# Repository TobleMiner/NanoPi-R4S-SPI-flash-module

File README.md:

NanoPi R4S NOR flash adapter
============================

This PCB provides the NanoPi R4S with NOR flash as a secondary or primary
boot option.  
Compared to most micro SD cards NOR flash is inherently much more reliable
due to its internal structure. While this comes with its own set of
drawbacks notably small storage size and low write speed it is very well
suited for many appliance applications.  
The dual LAN port configuration of the NanoPi R4S makes it a perfect match
for router operations. This NOR flash adapter module could for example be
paired with OpenWRT to provide a highly reliable router platform.

In addition to the SPI flash this board also features an STM32G031G6U6
microcontroller. It is connected to an I2C bus on the NanoPi R4S.  
The MCU has control over the reset and write protect lines of the SPI NOR
flash chip. Thus it can be used to disable the flash chip if booting from
alternate sources is desired. The write-protect line can be used to
implement custom tamper-proof storage designs.

To notify users of operations performed by the MCU a small dynamic
speaker is provided.

# Ordering

**WARNING: Do not order rev1.0 at JLC. The partnumber for the MCU is incorrect!**

The fabrication files inside `fab` are JLCPCB-ready. I'd suggest ordering
with a 1mm board thickness. This will ensure the easiest fit in small
cases.

The board can be fully assmebled by JLC. The required fabrication files
can also be found in the `fab` directory.  
If you do not plan on using the MCU on the board you can simply unselect
the following components on JLC's website during ordering:

- U5
- D1
- LS1
- C4
- C5
- C6

This will make the boards significantly cheaper, especially when ordering
small quantities.

# Installation

Due to space constraints imposed by many cases the recommended
installation method for this board is to solder it directly to the
expansion header of the NanoPi R4S. Make sure to push the board down onto
the expansion header as far as possible before soldering it into place.

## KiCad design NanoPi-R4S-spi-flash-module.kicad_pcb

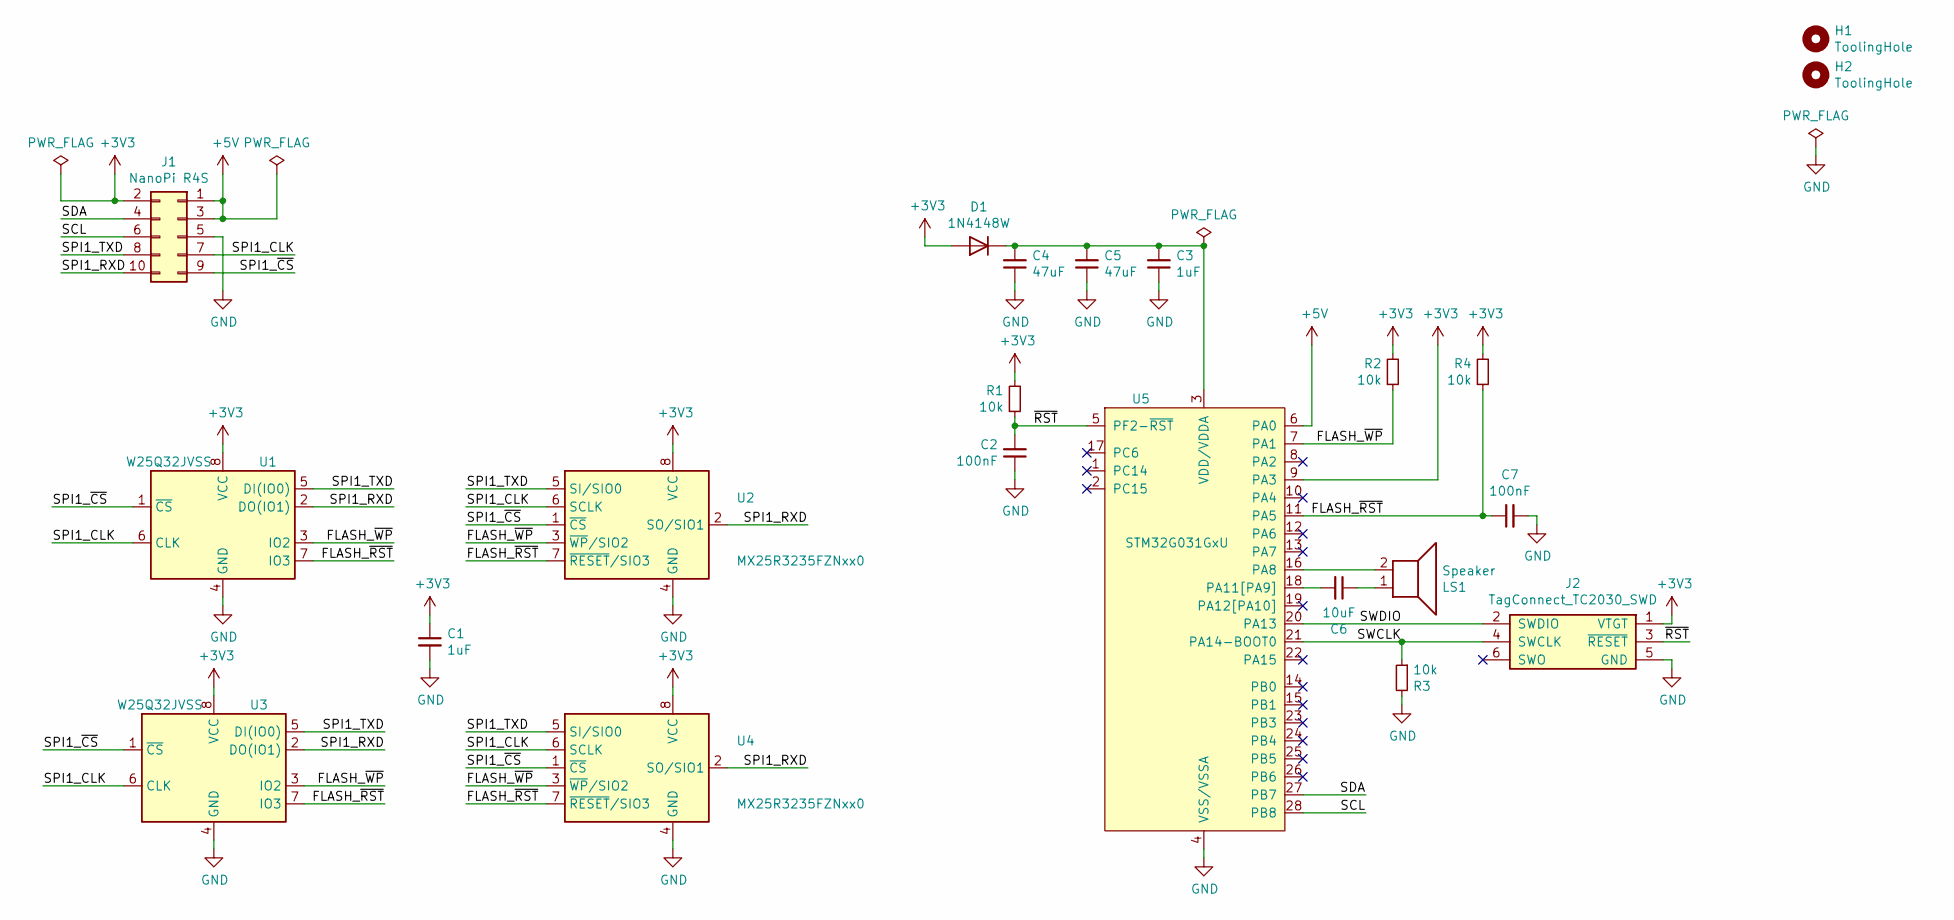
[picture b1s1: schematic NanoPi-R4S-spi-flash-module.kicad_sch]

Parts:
C1, C3: 1uF; C_0402_1005Metric; LCSC C52923
C2, C7: 100nF; C_0402_1005Metric; LCSC C1525
C4, C5: 47uF; C_0603_1608Metric; LCSC C140782
C6: 10uF; C_0402_1005Metric; LCSC C15525
D1: 1N4148W; D_SOD-123; LCSC C81598
H1, H2: ToolingHole; ToolingHole_JLCSMT
J1: NanoPi R4S; PinHeader_2x05_P2.54mm_Vertical
J2: TagConnect_TC2030_SWD; Tag-Connect_TC2030-IDC-NL_2x03_P1.27mm_Vertical
LS1: Speaker; MLT_7525; LCSC C95299
R1, R2, R3, R4: 10k; R_0402_1005Metric; LCSC C25744
U1: W25Q32JVSS; SOIC-8_5.23x5.23mm_P1.27mm; LCSC C190799
U2: MX25R3235FZNxx0; WSON-8-1EP_6x5mm_P1.27mm_EP3.4x4mm
U3: W25Q32JVSS; SOIC-8_7.5x5.85mm_P1.27mm
U4: MX25R3235FZNxx0; WSON-8-1EP_8x6mm_P1.27mm_EP3.4x4.3mm
U5: STM32G031GxU; Package_QFN_ST_ST_UFQFPN-28_4x4mm_P0.5mm; LCSC C432211

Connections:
+3V3: C1.1, D1.2 (A), J1.2, J2.1 (VTGT), R1.2, R2.2, R4.2, U1.8 (VCC), U2.8 (VCC), U3.8 (VCC), U4.8 (VCC), U5.9 (PA3)
+5V: J1.1, J1.3, U5.6 (PA0)
/FLASH_~RST: C7.1, R4.1, U1.7 (IO3), U2.7 (~RESET/SIO3), U3.7 (IO3), U4.7 (~RESET/SIO3), U5.11 (PA5)
/FLASH_~WP: R2.1, U1.3 (IO2), U2.3 (~WP/SIO2), U3.3 (IO2), U4.3 (~WP/SIO2), U5.7 (PA1)
/SCL: J1.6, U5.28 (PB8)
/SDA: J1.4, U5.27 (PB7)
/SPI1_CLK: J1.7, U1.6 (CLK), U2.6 (SCLK), U3.6 (CLK), U4.6 (SCLK)
/SPI1_RXD: J1.10, U1.2 (DO(IO1)), U2.2 (SO/SIO1), U3.2 (DO(IO1)), U4.2 (SO/SIO1)
/SPI1_TXD: J1.8, U1.5 (DI(IO0)), U2.5 (SI/SIO0), U3.5 (DI(IO0)), U4.5 (SI/SIO0)
/SPI1_~CS: J1.9, U1.1 (~CS), U2.1 (~CS), U3.1 (~CS), U4.1 (~CS)
/SWCLK: J2.4 (SWCLK), R3.1, U5.21 (PA14-BOOT0)
/SWDIO: J2.2 (SWDIO), U5.20 (PA13)
/~RST: C2.2, J2.3 (~RESET), R1.1, U5.5 (PF2-~RST)
GND: C1.2, C2.1, C3.1, C4.1, C5.1, C7.2, J1.5, J2.5 (GND), R3.2, U1.4 (GND), U2.4 (GND), U2.9 (GND), U3.4 (GND), U4.4 (GND), U4.9 (GND), U5.4 (VSS/VSSA)
unnamed: C3.2, C4.2, C5.2, D1.1 (K), U5.3 (VDD/VDDA)
unnamed: C6.1, LS1.1
unnamed: C6.2, U5.18 (PA11[PA9])
unnamed: LS1.2, U5.16 (PA8)

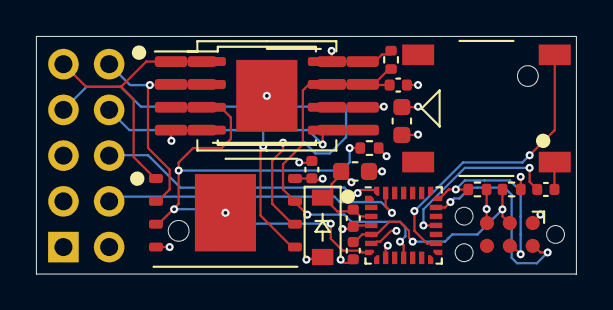
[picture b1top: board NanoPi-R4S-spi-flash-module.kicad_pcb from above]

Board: 4 copper layers, 30.0 x 13.2 mm, 22 parts (1 on the bottom side), 18 nets.

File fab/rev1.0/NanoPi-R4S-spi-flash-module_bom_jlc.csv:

"Comment","Designator","Footprint","LCSC Part #"
"1uF","C1,C3","C_0402_1005Metric","C52923"
"100nF","C2,C7","C_0402_1005Metric","C1525"
"47uF","C5,C4","C_0603_1608Metric","C140782"
"10uF","C6","C_0402_1005Metric","C15525"
"1N4248W","D1","D_SOD-123","C81598"
"Speaker","LS1","MLT_7525","C95299"
"10k","R1,R2,R4,R3","R_0402_1005Metric","C25744"
"W25Q32JVSS","U1","SOIC-8_5.23x5.23mm_P1.27mm","C190799"
"STM32G031GxU","U5","Package_QFN_ST_ST_UFQFPN-28_4x4mm_P0.5mm","C96514"

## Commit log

2021-12-18 Remove superfluous fab.zip file
    Fabrication files are in /fab
2021-12-18 Ignore local fab.zip fabrication file bundles
2021-12-18 Improve wording
2021-12-18 Fix typo
2021-12-19 Replace D1 by regular silicon diode
    Schottky diodes tend to have high leakage current. Considering the MCU is
    supposed to be kept running on C4 and C5 as long as possible after power
    has been removed reducing leakage current back into the 3.3V supply rail
    is key.
    Replace D1 by an ordinary 1N4148 to minimize leakage current back into the
    3.3V supply rail.
2021-12-19 Hide D1 designator
2022-01-04 Fix incorrect MCU partnumber
2022-01-04 Rev 1.1
    Changelog:
    - fix incorrect MCU JLC partnumber
